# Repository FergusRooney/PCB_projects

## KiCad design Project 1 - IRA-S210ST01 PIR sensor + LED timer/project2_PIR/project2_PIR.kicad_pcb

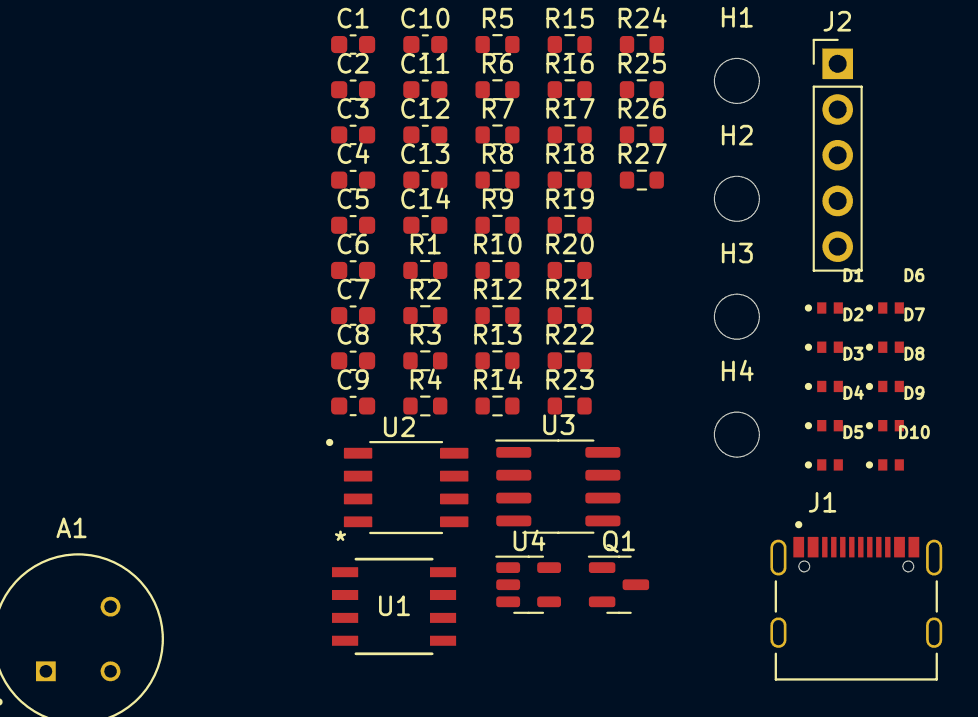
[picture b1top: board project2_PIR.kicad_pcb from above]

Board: 2 copper layers, 62 parts (0 on the bottom side), 22 nets, no tracks yet.

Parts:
A1: IRA-S210ST01; TO254P940H490-3
C1, C7, C8: 0.1u; C_0603_1608Metric
C2, C4, C10, C12: 22u; C_0603_1608Metric
C3, C5, C11: 10n; C_0603_1608Metric
C6, C9, C13: 1u; C_0603_1608Metric
C14: 1n; C_0603_1608Metric
D1, D2, D3, D4, D5, D6, D7, D8, D9, D10: LED; LEDC1005X25N__EAST10052WA0
H1, H2, H3, H4: MountingHole; MountingHole_2.5mm
J1: TYPE-C-31-M-12; HRO_TYPE-C-31-M-12
J2: Conn_01x05; PinHeader_1x05_P2.54mm_Vertical
Q1: 2N7002; SOT-23
R1: 5.2k; R_0603_1608Metric
R2: 5.1K; R_0603_1608Metric
R3: 1R0; R_0603_1608Metric
R4, R6: 22k; R_0603_1608Metric
R5, R7: 1.2M; R_0603_1608Metric
R8, R9: 100k; R_0603_1608Metric
R10: 47k; R_0603_1608Metric
R12: 10k; R_0603_1608Metric
R13, R14, R15, R16, R17, R18, R19, R23, R24, R25: 140; R_0603_1608Metric
R20, R27: 68k; R_0603_1608Metric
R21, R26: 39k; R_0603_1608Metric
R22: 2.1M; R_0603_1608Metric
U1: LM393; SOIC-8-LM393D
U2: MCP602; SOIC-8-MCP602-I_SN
U3: NE555D; SOIC-8_3.9x4.9mm_P1.27mm
U4: TLV70033_SOT23-5; SOT-23-5

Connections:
+3.3V: C8.2, C9.2, C13.2, R3.2, R8.1, R20.1, U2.8 (V+), U4.5 (OUT)
/LED_NMOS_GATE: J2.5, U3.3 (Q)
/PIR_AMP_FILT: C5.2, J2.3, R7.1, U1.3 (+), U1.6 (-), U2.7
/SENSED_HUMAN: J2.4, R12.2, U1.1, U1.7, U3.2 (TR)
GND: A1.3 (GND), C1.2, C2.2, C6.1, C7.1, C8.1, C9.1, C10.2, C11.1, C12.1, C13.1, C14.2, J1.A1_B12 (GND), J1.B1_A12 (GND), J1.S1 (SHIELD), J1.S2 (SHIELD), J1.S3 (SHIELD), J1.S4 (SHIELD), J2.2, Q1.3 (S), R1.2, R2.2, R9.2, R10.1, R27.2, U1.4 (V-), U2.4 (V-), U3.1 (GND), U4.2 (GND)
unnamed: A1.1 (DRAIN), C1.1, C10.1, R3.1
unnamed: A1.2 (SOURCE), C14.1, R10.2, U2.3 (+)
unnamed: C2.1, R4.1
unnamed: C3.2, C4.1, R5.1, U2.1
unnamed: C4.2, R6.2
unnamed: J1.A5 (CC1), R1.1
unnamed: J1.B5 (CC2), R2.1
unnamed: Q1.1 (D), R13.2, R14.2, R15.2, R16.2, R17.2, R18.2, R19.2, R23.2, R24.2, R25.2
unnamed: R21.2, R26.1
unnamed: R20.2, R21.1, U1.2 (-)
unnamed: R26.2, R27.1, U1.5 (+)
unnamed: C3.1, R4.2, R5.2, U2.2 (-)
unnamed: R8.2, R9.1, U2.5 (+)
unnamed: C5.1, R6.1, R7.2, U2.6 (-)
unnamed: C11.2, U3.5 (CV)
unnamed: C12.2, R22.2, U3.6 (THR), U3.7 (DIS)
VBUS: C6.2, C7.2, J1.A4_B9 (VBUS), J1.B4_A9 (VBUS), J2.1, R12.1, R22.1, U1.8 (V+), U3.4 (R), U3.8 (VCC), U4.1 (IN), U4.3 (EN)

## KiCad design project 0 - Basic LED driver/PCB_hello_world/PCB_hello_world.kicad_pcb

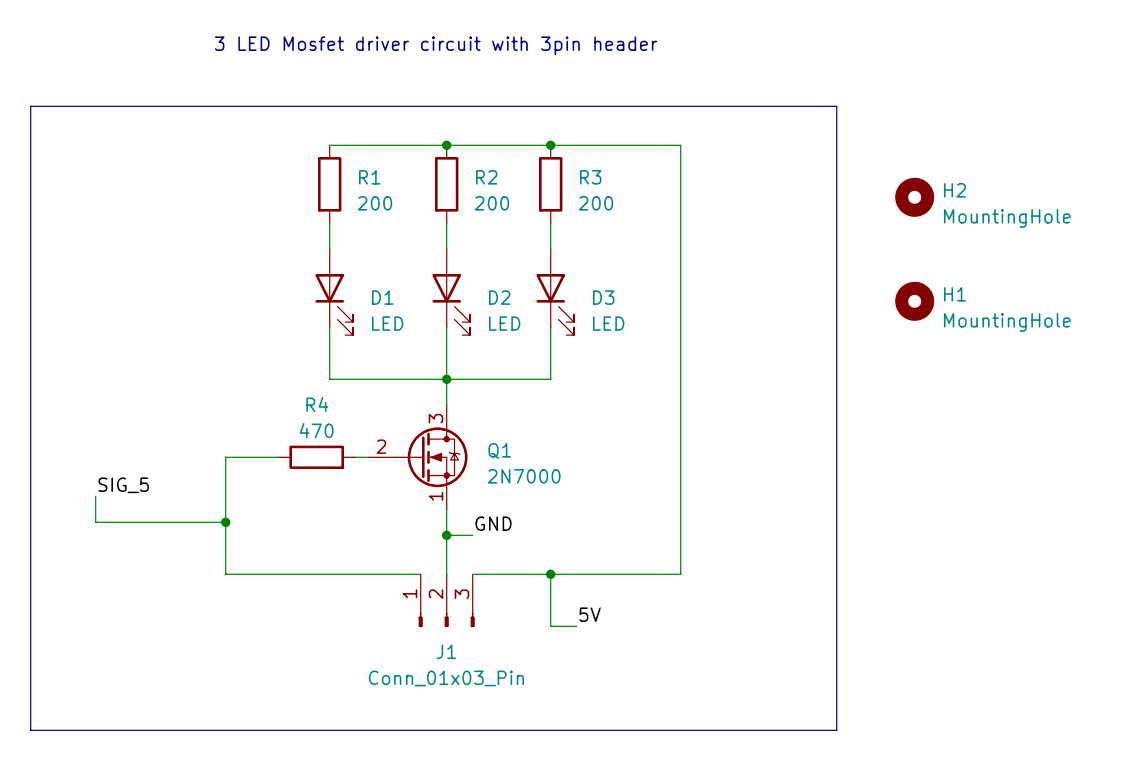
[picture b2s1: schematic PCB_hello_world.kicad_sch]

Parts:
D1: LED; LED_D5.0mm_Horizontal_O1.27mm_Z3.0mm
D2, D3: LED; LED_D5.0mm_Horizontal_O1.27mm_Z3.0mm; JLCPCB Part # C397053
H1, H2: MountingHole; MountingHole_2.2mm_M2_DIN965_Pad_TopBottom
J1: Conn_01x03_Pin; PinHeader_1x03_P2.54mm_Horizontal; JLCPCB Part # C706866
Q1: 2N7000; TO-92_Inline; JLCPCB Part # C9114
R1, R2, R3: 200; R_Axial_DIN0207_L6.3mm_D2.5mm_P7.62mm_Horizontal
R4: 470; R_Axial_DIN0207_L6.3mm_D2.5mm_P7.62mm_Horizontal; part ROX1SJ470R

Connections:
/5V: J1.3, R1.1, R2.1, R3.1
/GND: J1.2, Q1.1 (S)
/SIG_5: J1.1, R4.1
unnamed: D1.2 (A), R1.2
unnamed: D1.1 (K), D2.1 (K), D3.1 (K), Q1.3 (D)
unnamed: D2.2 (A), R2.2
unnamed: D3.2 (A), R3.2
unnamed: Q1.2 (G), R4.2

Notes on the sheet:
3 LED Mosfet driver circuit with 3pin header

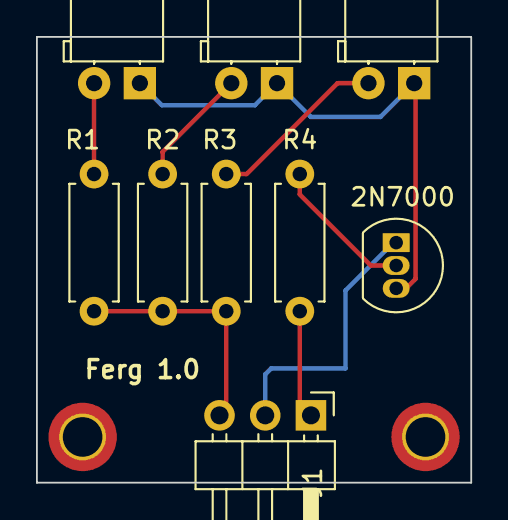
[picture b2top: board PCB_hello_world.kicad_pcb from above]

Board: 2 copper layers, 24.1 x 24.8 mm, 11 parts (0 on the bottom side), 8 nets.

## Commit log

2023-06-02 rename PIR project
